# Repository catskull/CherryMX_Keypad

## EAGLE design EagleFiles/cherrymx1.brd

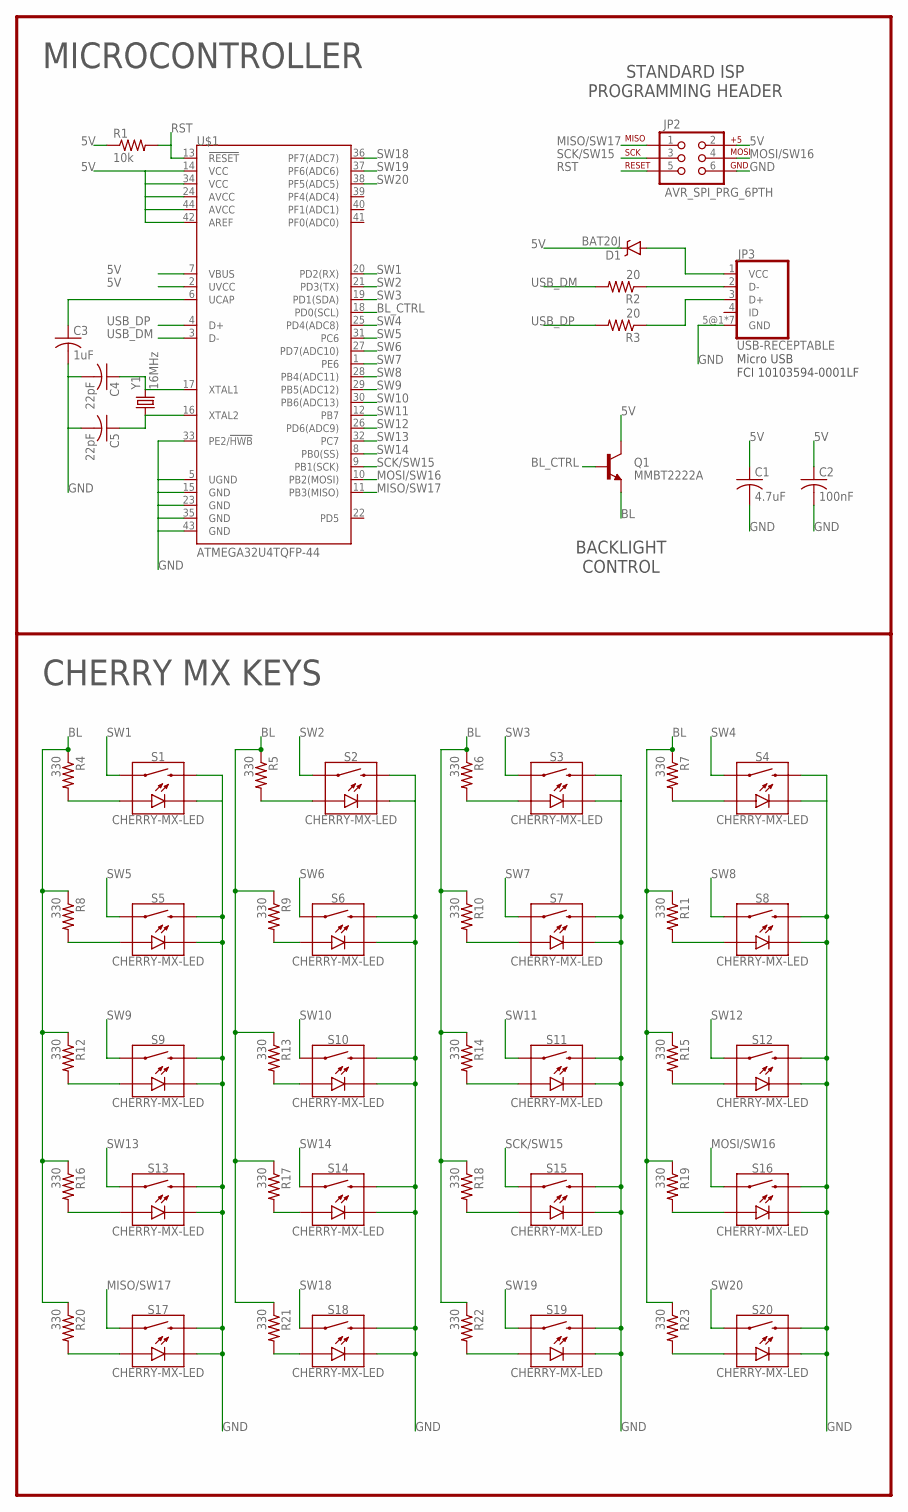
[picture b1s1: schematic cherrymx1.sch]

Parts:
C1: 4.7uF; C0603
C2: 100nF; C0603
C3: 1uF; C0603
C4, C5: 22pF; C0603
D1: BAT20J; SOD-323
JP2: AVR_SPI_PRG_6PTH; 2X3
JP3: USB-RECEPTABLE; FCI-10103594-0001LF
Q1: MMBT2222A; SOT23-3
R1: 10k; R0603
R2, R3: 20; R0603
R4, R5, R6, R7, R8, R9, R10, R11, R12, R13, R14, R15, R16, R17, R18, R19, R20, R21, R22, R23: 330; R0603
S1, S2, S3, S4, S5, S6, S7, S8, S9, S10, S11, S12, S13, S14, S15, S16, S17, S18, S19, S20: CHERRY-MX-LED
U$1: ATMEGA32U4TQFP-44; TQFP44
Y1: 16MHz; CRYSTAL-SMD-5X3

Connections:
5V: C1.1, C2.1, D1.C, JP2.2, Q1.3 (C), R1.1, U$1.2 (UVCC), U$1.7 (VBUS), U$1.14 (VCC), U$1.24 (AVCC), U$1.34 (VCC), U$1.42 (AREF), U$1.44 (AVCC)
BL: Q1.2 (E), R4.1, R5.1, R6.1, R7.1, R8.1, R9.1, R10.1, R11.1, R12.1, R13.1, R14.1, R15.1, R16.1, R17.1, R18.1, R19.1, R20.1, R21.1, R22.1, R23.1
BL_CTRL: Q1.1 (B), U$1.18 (PD0(SCL))
GND: C1.2, C2.2, C3.2, C4.2, C5.2, JP2.6, JP3.5@1 (GND), JP3.5@2 (GND), JP3.5@3 (GND), JP3.5@4 (GND), JP3.5@5 (GND), JP3.5@6 (GND), JP3.5@7 (GND), S1.K (C), S1.S2, S2.K (C), S2.S2, S3.K (C), S3.S2, S4.K (C), S4.S2, S5.K (C), S5.S2, S6.K (C), S6.S2, S7.K (C), S7.S2, S8.K (C), S8.S2, S9.K (C), S9.S2, S10.K (C), S10.S2, S11.K (C), S11.S2, S12.K (C), S12.S2, S13.K (C), S13.S2, S14.K (C), S14.S2, S15.K (C), S15.S2, S16.K (C), S16.S2, S17.K (C), S17.S2, S18.K (C), S18.S2, S19.K (C), S19.S2, S20.K (C), S20.S2, U$1.5 (UGND), U$1.15 (GND), U$1.23 (GND), U$1.33 (PE2/!HWB), U$1.35 (GND), U$1.43 (GND)
MISO/SW17: JP2.1, S17.S1, U$1.11 (PB3(MISO))
MOSI/SW16: JP2.4, S16.S1, U$1.10 (PB2(MOSI))
unnamed: D1.A, JP3.1 (VCC)
unnamed: JP3.2 (D-), R2.1
unnamed: JP3.3 (D+), R3.1
unnamed: R8.2, S5.A
unnamed: C3.1, U$1.6 (UCAP)
unnamed: C4.1, U$1.17 (XTAL1), Y1.3 (2)
unnamed: R12.2, S9.A
unnamed: C5.1, U$1.16 (XTAL2), Y1.1
unnamed: R4.2, S1.A
unnamed: R6.2, S3.A
unnamed: R7.2, S4.A
unnamed: R5.2, S2.A
unnamed: R16.2, S13.A
unnamed: R20.2, S17.A
unnamed: R21.2, S18.A
unnamed: R17.2, S14.A
unnamed: R13.2, S10.A
unnamed: R9.2, S6.A
unnamed: R22.2, S19.A
unnamed: R18.2, S15.A
unnamed: R14.2, S11.A
unnamed: R10.2, S7.A
unnamed: R23.2, S20.A
unnamed: R19.2, S16.A
unnamed: R15.2, S12.A
unnamed: R11.2, S8.A
RST: JP2.5, R1.2, U$1.13 (!RESET)
SCK/SW15: JP2.3, S15.S1, U$1.9 (PB1(SCK))
SW1: S1.S1, U$1.20 (PD2(RX))
SW2: S2.S1, U$1.21 (PD3(TX))
SW3: S3.S1, U$1.19 (PD1(SDA))
SW4: S4.S1, U$1.25 (PD4(ADC8))
SW5: S5.S1, U$1.31 (PC6)
SW6: S6.S1, U$1.27 (PD7(ADC10))
SW7: S7.S1, U$1.1 (PE6)
SW8: S8.S1, U$1.28 (PB4(ADC11))
SW9: S9.S1, U$1.29 (PB5(ADC12))
SW10: S10.S1, U$1.30 (PB6(ADC13))
SW11: S11.S1, U$1.12 (PB7)
SW12: S12.S1, U$1.26 (PD6(ADC9))
SW13: S13.S1, U$1.32 (PC7)
SW14: S14.S1, U$1.8 (PB0(SS))
SW18: S18.S1, U$1.36 (PF7(ADC7))
SW19: S19.S1, U$1.37 (PF6(ADC6))
SW20: S20.S1, U$1.38 (PF5(ADC5))
USB_DM: R2.2, U$1.3 (D-)
USB_DP: R3.2, U$1.4 (D+)

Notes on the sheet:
Micro USB FCI 10103594-0001LF
MICROCONTROLLER
CHERRY MX KEYS
BACKLIGHT CONTROL
STANDARD ISP PROGRAMMING HEADER

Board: 2 copper layers, 55 parts (0 on the bottom side), 53 nets, no tracks yet.

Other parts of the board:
U$2: OSHW-LOGO-M

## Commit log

2016-06-20 Update gitignore
2016-06-20 Add a bunch more switches!

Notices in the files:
parts and their libraries:
SparkFun-Electromechanical2: Licensing: Creative Commons ShareAlike 4.0 International - https://creativecommons.org/licenses/by-sa/4.0
